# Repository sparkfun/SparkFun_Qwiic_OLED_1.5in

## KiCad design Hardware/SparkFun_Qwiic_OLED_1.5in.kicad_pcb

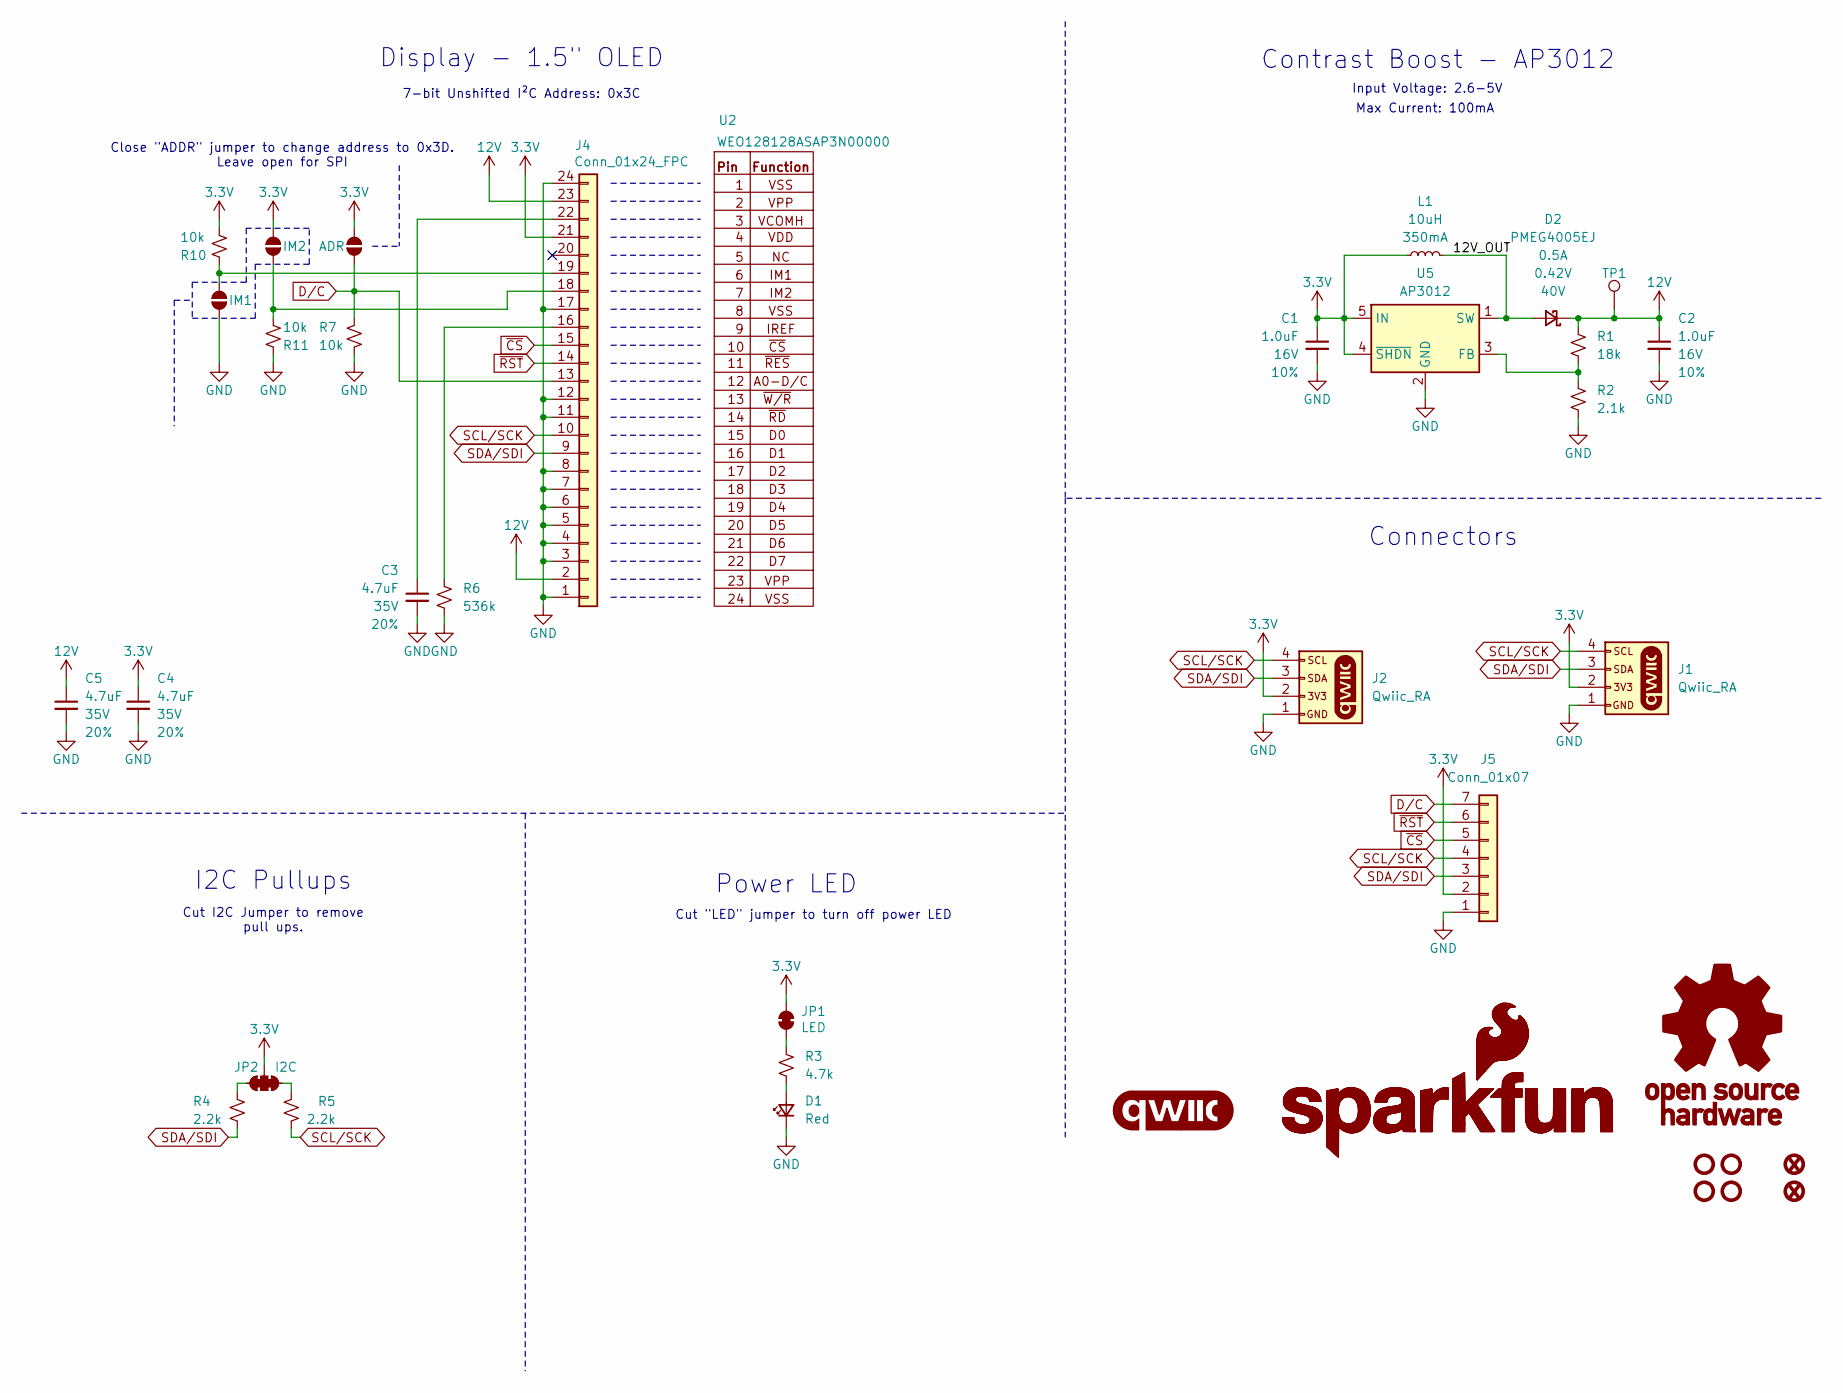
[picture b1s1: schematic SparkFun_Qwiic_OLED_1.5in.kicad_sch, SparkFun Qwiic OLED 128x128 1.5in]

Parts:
C1, C2: 1.0uF; C_0603_1608Metric; Voltage 16V; Tolerance 10%
C3, C4, C5: 4.7uF; C_0603_1608Metric; Voltage 35V; Tolerance 20%
D1: Red; LED_0603_1608Metric_Red
D2: PMEG4005EJ; SOD-323
FID3, FID4: Fiducial_0.5mm; Fiducial_0.5mm_Mask1mm
G1: qwiic_Logo
G2: SparkFun_Logo; SparkFun_Logo_8mm
G3: SparkFun_Logo
G4: OSHW_Logo; Creative_Commons_License
J1, J2: Qwiic_RA; JST_SMD_1.0mm-4_Black
J4: Conn_01x24_FPC; FPC_0.5mm-24
J5: Conn_01x07; 1x07
JP1: LED; Jumper_2_NC_Trace
JP2: I2C; Jumper_3_NC-2_Trace
JP3: ADR; Jumper_2_NO
JP6: IM1; Jumper_2_NO
JP7: IM2; Jumper_2_NO
L1: 10uH; C_0805_2012Metric
R1: 18k; R_0603_1608Metric
R2: 2.1k; R_0603_1608Metric
R3: 4.7k; R_0603_1608Metric
R4, R5: 2.2k; R_0603_1608Metric
R6: 536k; R_0603_1608Metric
R7, R10, R11: 10k; R_0603_1608Metric
ST1, ST2, ST3, ST4: Standoff
TP1: 1.0mm; TestPoint-1.0mm
U2: WEO128128ASAP3N00000; OLED_1.5in_128x128-Folded
U5: AP3012; SOT23-5

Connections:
3.3V: C1.1, C4.1, J1.2, J2.2, J4.21, J5.2, JP1.2 (B), JP2.2 (B), JP3.2 (B), JP7.2 (B), L1.1, R10.1, U5.4 (~SHDN), U5.5 (IN)
12V: C2.1, C5.1, D2.1 (K), J4.2, J4.23, R1.2, TP1.1
/12V_OUT: D2.2 (A), L1.2, U5.1 (SW)
D/C: J4.13, J5.7, JP3.1 (A), R7.2
GND: C1.2, C2.2, C3.2, C4.2, C5.2, D1.1 (K), J1.1, J2.1, J4.1, J4.3, J4.4, J4.5, J4.6, J4.7, J4.8, J4.11, J4.12, J4.17, J4.24, J5.1, JP6.1 (A), R2.1, R6.1, R7.1, R11.2, U5.2 (GND)
unnamed: D1.2 (A), R3.1
unnamed: J4.16, R6.2
unnamed: J4.18, JP7.1 (A), R11.1
unnamed: J4.19, JP6.2 (B), R10.2
unnamed: C3.1, J4.22
unnamed: JP1.1 (A), R3.2
unnamed: JP2.1 (A), R5.1
unnamed: JP2.3 (C), R4.2
unnamed: R1.1, R2.2, U5.3 (FB)
SCL/SCK: J1.4, J2.4, J4.10, J5.4, R5.2
SDA/SDI: J1.3, J2.3, J4.9, J5.3, R4.1
~CS: J4.15, J5.5
~RST: J4.14, J5.6

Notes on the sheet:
Input Voltage: 2.6-5V
Cut I2C Jumper to remove pull ups.
Display - 1.5" OLED
Max Current: 100mA
Cut "LED" jumper to turn off power LED
Power LED
Close "ADDR" jumper to change address to 0x3D. Leave open for SPI
7-bit Unshifted I²C Address: 0x3C
Connectors
I2C Pullups
Contrast Boost - AP3012

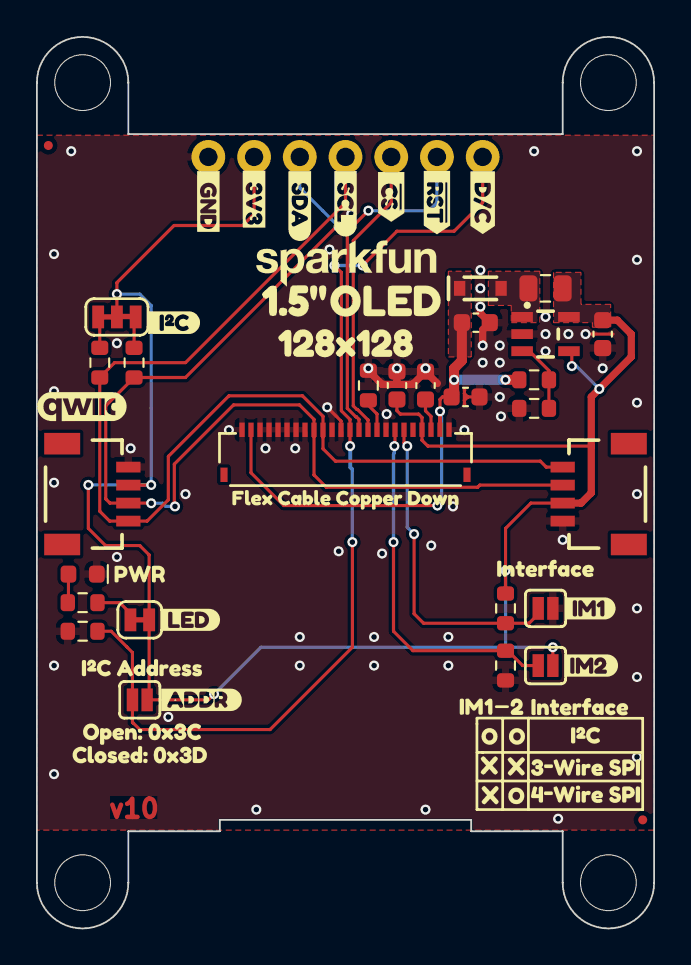
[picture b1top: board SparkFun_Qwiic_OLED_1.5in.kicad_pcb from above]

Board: 2 copper layers, 34.3 x 49.5 mm, 70 parts (1 on the bottom side), 18 nets.

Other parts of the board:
kibuzzard-65A8A8B4: G***; kibuzzard-65A8A8B4
kibuzzard-67BF7EBF: G***; kibuzzard-67BF7EBF
kibuzzard-67BF7ED9: G***; kibuzzard-67BF7ED9
kibuzzard-67BF7F2F: G***; kibuzzard-67BF7F2F
kibuzzard-67BF7F13: G***; kibuzzard-67BF7F13
kibuzzard-680E7A4B: G***; kibuzzard-680E7A4B
kibuzzard-680E7A69: G***; kibuzzard-680E7A69
kibuzzard-680FC73E: G***; kibuzzard-680FC73E
kibuzzard-680FC89E: G***; kibuzzard-680FC89E
kibuzzard-680FC883: G***; kibuzzard-680FC883
kibuzzard-680FC897: G***; kibuzzard-680FC897
kibuzzard-680FC957: G***; kibuzzard-680FC957
kibuzzard-680FCA9D: G***; kibuzzard-680FCA9D
kibuzzard-680FCA96: G***; kibuzzard-680FCA96
kibuzzard-680FCADD: G***; kibuzzard-680FCADD
kibuzzard-680FCAEB: G***; kibuzzard-680FCAEB
kibuzzard-684C656A: G***; kibuzzard-684C656A
kibuzzard-685B1775: G***; kibuzzard-685B1775
kibuzzard-6893A61C, kibuzzard-6893A61C#2, kibuzzard-6893A61C#3: G***; kibuzzard-6893A61C
kibuzzard-689381EF, kibuzzard-689381EF#2, kibuzzard-689381EF#3: G***; kibuzzard-689381EF
kibuzzard-6851867B: G***; kibuzzard-6851867B
kibuzzard-6851871B: G***; kibuzzard-6851871B
kibuzzard-6893822D: G***; kibuzzard-6893822D
kibuzzard-6893824B: G***; kibuzzard-6893824B
kibuzzard-68518672: G***; kibuzzard-68518672
kibuzzard-68938236: G***; kibuzzard-68938236
kibuzzard-68938244: G***; kibuzzard-68938244
kibuzzard-68938257: G***; kibuzzard-68938257
kibuzzard-68938266: G***; kibuzzard-68938266
kibuzzard-68938270: G***; kibuzzard-68938270

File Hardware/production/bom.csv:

Designator,Footprint,Quantity,Value,LCSC Part #
"C1, C2",603,2,1.0uF,
"C3, C4, C5",603,3,4.7uF,
D1,603,1,Red,
D2,SOD-323,1,PMEG4005EJ,
"J1, J2",JST_SMD_1.0mm-4_Black,2,Qwiic_RA,
J3,1x06,1,Conn_01x06,
J4,FPC_0.5mm-24,1,Conn_01x24_FPC,
L1,805,1,10uH,
"R10, R11, R7",603,3,10k,
R12,603,1,68.1k,
R3,603,1,4.7k,
"R4, R5",603,2,2.2k,
R6,603,1,569k,
R9,603,1,7.5k,
U5,SOT23-5,1,AP3012,

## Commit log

2025-06-11 Updates the display part to be it's own symbol
2025-06-11 Removes connector from OLED symbol
2025-06-13 Removes connector from OLED symbolbol and footprint
2025-06-13 Aligns the power circuitry to the IC's specification
2025-06-13 Routes the power circuitry
2025-06-13 Adds another pour for 3.3V at the power circuitry
2025-06-13 Routes all traces
2025-06-13 Cleans up the routing
2025-06-13 Moves some silk
2025-06-17 Adds vias, moves silk around, moves version to v01
2025-06-17 Changes the 12V_OUT label to be more discrete
2025-06-24 Updates the text within the schematic to be more clear
2025-06-24 Fixes board outline
2025-06-24 Fixes some DRC errors
2025-06-24 Moves some vias so that it doesn't interfere with silk
2025-06-24 Adds bom positions and list for ordering
2025-06-24 Adds no-connect on pin 5, adds prod-id value for 569k resistor
2025-06-24 Updates PCB with aforementioned changes
2025-06-24 Adds D/C to PTH header for SPI funcitonality
2025-06-26 Changes certain resistors to use more common values
2025-07-31 Adds CH1120 datasheet
2025-08-06 Updates to v10
2025-08-06 Cleans up schematic, adds table to silk for interface settings
2025-08-06 Fixes the qwiic connectors being misaligned, updates measures
2025-08-06 Increases the size of the board by .05", moves the FPC connector over .0065" so that it's in the center
2025-08-06 Centers PTH headers and screen, fixes some DRC errors created by moving the FPC connector over that small amount
2025-08-06 Fixes some text on the LED jumper
2025-08-06 Adds some "O"'s to indicate open on the interface table
2025-08-12 Adds "I2C" to address in schematic, removes stub
2025-08-12 Moves the connector up .05" so that the FPC cable is a bit tighter to the PCB when the screen is secured ot it
2025-08-12 Updates the OLED footprint so that the screen to fold distance is more correctly represented
2025-08-12 Moves some small traces around
2025-08-12 Increases the size of the "V-score" text
2025-08-26 Replaces the 536k part with a 549k part
2025-09-11 Initial docs commit
    Adding initial files for GH pages docs with updates from template.
2025-12-18 Docs update
    Docs review update. Adding photos & review changes.
2025-12-18 Adding GH Pages build file
2025-12-19 Deployed d569666 with MkDocs version: 1.6.1
2026-06-03 Deployed 1e33162 with MkDocs version: 1.6.1

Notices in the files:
parts and their libraries:
https://creativecommons.org/licenses/by-sa/4.0
Released under the Creative Commons Attribution Share-Alike 4.0 License
